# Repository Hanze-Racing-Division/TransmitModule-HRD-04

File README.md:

# TransmitModule-HRD-04
Communication module

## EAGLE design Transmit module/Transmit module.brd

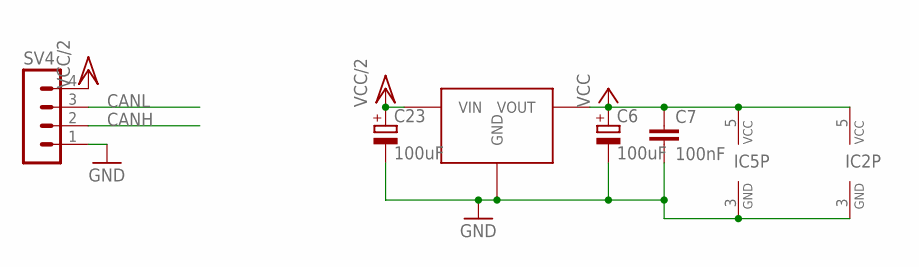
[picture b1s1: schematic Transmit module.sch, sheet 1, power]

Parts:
C6, C23: 100uF; 153CLV-0605; FARNELL 1244406RL
C7: 100nF; C0805
IC2, IC5: 74AHCT1G14DBV; SOT23-5
SV4: MA04-1
U$2: TS2940; TO-252

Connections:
CANH: SV4.2; also elsewhere on the board
CANL: SV4.3; also elsewhere on the board
GND: C6.-, C7.2, C23.-, IC2.3 (GND), IC5.3 (GND), SV4.1, U$2.GND; also elsewhere on the board
VCC: C6.+, C7.1, IC2.5 (VCC), IC5.5 (VCC), U$2.VOUT; also elsewhere on the board
VCC/2: C23.+, SV4.4, U$2.VIN; also elsewhere on the board

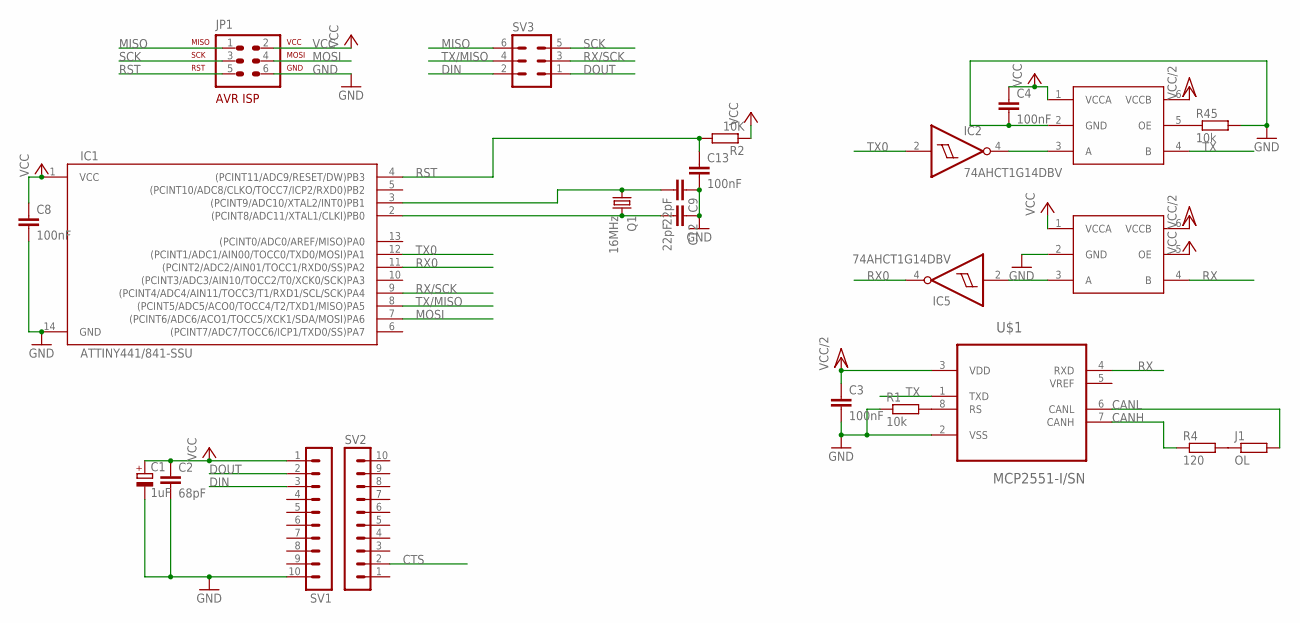
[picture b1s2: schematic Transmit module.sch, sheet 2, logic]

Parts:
C1: 1uF; 153CLV-0505; FARNELL 1714751
C2: 68pF; C0805; FARNELL 2497040
C3, C4, C8, C13: 100nF; C0805
C9, C12: 22pF; C0805
IC1: ATTINY441/841-SSU; SOIC14N; FARNELL 2396716
IC2, IC5: 74AHCT1G14DBV; SOT23-5
J1: OL; R0805
JP1: AVR-ISP-6VERT; AVR-ISP-6
Q1: 16MHz; HC49UP
R1: 10k; M0805
R2: 10K; R0805
R4: 120; R0805
R45: 10k; R0805
SV1, SV2: MA10-1
SV3: MA03-2
U$1: MCP2551-I/SN; SOIC127P600X175-8N
U$3, U$4: TXB0101; TSOT23-6_DDC

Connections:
CANH: R4.1, U$1.7 (CANH); also elsewhere on the board
CANL: J1.2, U$1.6 (CANL); also elsewhere on the board
CTS: SV2.2
DIN: SV1.3, SV3.2
DOUT: SV1.2, SV3.1
GND: C1.-, C2.2, C3.2, C4.2, C8.2, C9.1, C12.1, C13.2, IC1.14 (GND), JP1.6, R1.1, R45.2, SV1.10, U$1.2 (VSS), U$3.2 (GND), U$4.2 (GND); also elsewhere on the board
MISO: JP1.1, SV3.6
MOSI: IC1.7 ((PCINT6/ADC6/ACO1/TOCC5/XCK1/SDA/MOSI)P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), JP1.4
unnamed: R1.2, U$1.8 (RS)
unnamed: R45.1, U$3.5 (OE)
unnamed: C9.2, IC1.3 ((PCINT9/ADC10/XTAL2/INT0)PB1), Q1.1
unnamed: C12.2, IC1.2 ((PCINT8/ADC11/XTAL1/CLKI)PB0), Q1.2
unnamed: IC2.4 (O), U$3.3 (A)
unnamed: IC5.2 (I), U$4.3 (A)
unnamed: J1.1, R4.2
RST: C13.1, IC1.4 ((PCINT11/ADC9/RESET/DW)PB3), JP1.5, R2.2
RX: U$1.4 (RXD), U$4.4 (B)
RX0: IC1.11 ((PCINT2/ADC2/AIN01/TOCC1/RXD0/SS)PA2), IC5.4 (O)
RX/SCK: IC1.9 ((PCINT4/ADC4/AIN11/TOCC3/T1/RXD1/SCL/SC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), SV3.3
SCK: JP1.3, SV3.5
TX: U$1.1 (TXD), U$3.4 (B)
TX0: IC1.12 ((PCINT1/ADC1/AIN00/TOCC0/TXD0/MOSI)PA1), IC2.2 (I)
TX/MISO: IC1.8 ((PCINT5/ADC5/ACO0/TOCC4/T2/TXD1/MISO)PA5), SV3.4
VCC: C1.+, C2.1, C4.1, C8.1, IC1.1 (VCC), JP1.2, R2.1, SV1.1, U$3.1 (VCCA), U$4.1 (VCCA), U$4.5 (OE); also elsewhere on the board
VCC/2: C3.1, U$1.3 (VDD), U$3.6 (VCCB), U$4.6 (VCCB); also elsewhere on the board

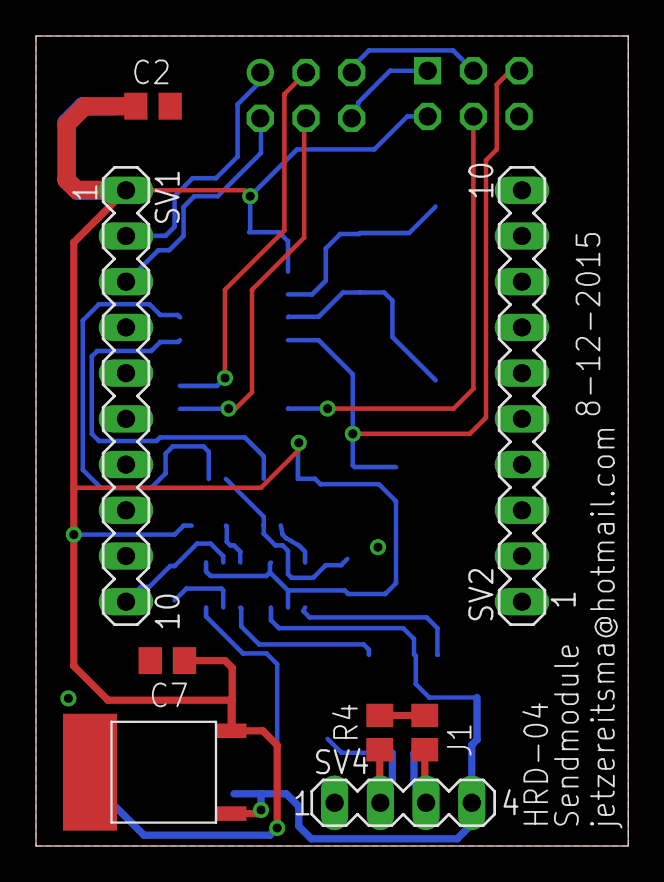
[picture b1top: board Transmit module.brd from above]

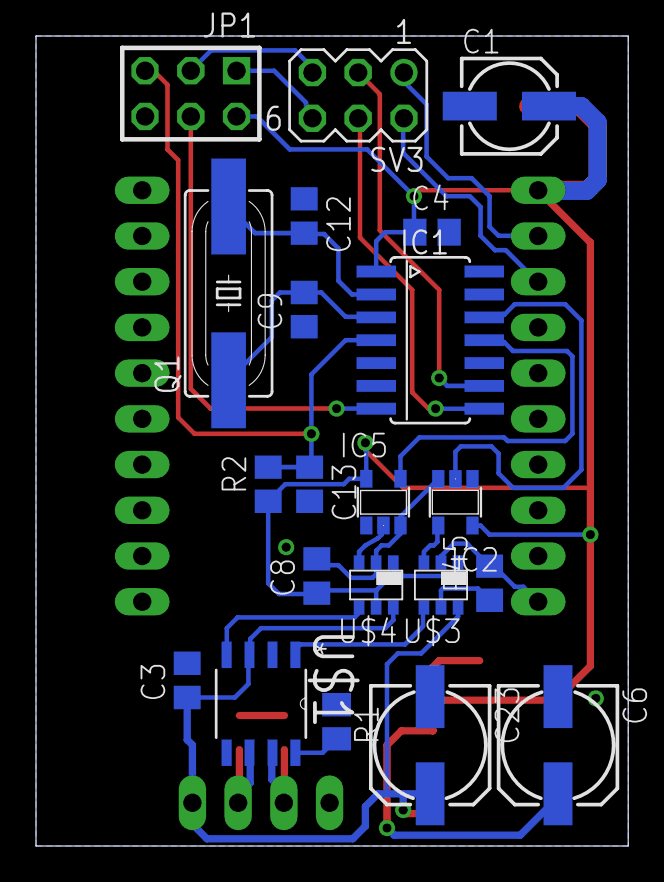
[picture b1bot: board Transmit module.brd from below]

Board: 2 copper layers, 32.9 x 45.0 mm, 29 parts (21 on the bottom side), 24 nets.

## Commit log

2016-04-21 added eagle files
